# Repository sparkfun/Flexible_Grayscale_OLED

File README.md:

SparkFun Flexible Grayscale OLED Display Breakout Board
========================================

[*SparkFun Flexible Grayscale Display - 1.81" (LCD-14606)*](https://www.sparkfun.com/products/14606)

This is a small flexible, grayscale OLED display. That’s right, we said flexible. We’ve been hearing about flexible displays for years, it’s finally here! You can’t fold it like paper but this OLED from Wisechip can be bent to a 40mm radius without damage. The display is than 0.5mm thick, less than 0.5 grams, and can display some impressive graphics with great contrast.

The carrier board generates the 12V required to drive the OLED display. The carrier board also has a signal buffer so that you can drive the display from any 3.3V or 5V microcontroller. However, because of the nature of the TXB0104 you must power the board with 3.5V or more. Your microcontroller can be 3.3V or 5V but we recommend you power the carrier board with 5V.

Repository Contents
-------------------

* **/Datasheets** - Datasheets explaining screen characteristics
* **/Hardware** - Eagle design files (.brd, .sch)
* **/Production** - Test bed files and production panel files.

Documentation
--------------
* **[Arduino Library](https://github.com/sparkfun/SparkFun_SSD1320_OLED_Arduino_Library)** - Arduino library for drawing, graphics, text, etc.
* **[BMP to Array](https://github.com/sparkfun/BMPtoArray)** - Python script to convert bitmaps to an Arduino prog_mem array when outputting grayscale images to OLEDs.
* **[Hookup Guide](https://learn.sparkfun.com/tutorials/flexible-grayscale-oled-hookup-guide)** - Basic hookup guide for the SparkFun Flexible Grayscale OLED Display.

License Information
-------------------

This product is _**open source**_! 

Please review the LICENSE.md file for license information. 

If you have any questions or concerns on licensing, please contact techsupport@sparkfun.com.

Please use, reuse, and modify these files as you see fit. Please maintain attribution to SparkFun Electronics and release anyThing Development Board derivative under the same license.

Distributed as-is; no warranty is given.

- Your friends at SparkFun.

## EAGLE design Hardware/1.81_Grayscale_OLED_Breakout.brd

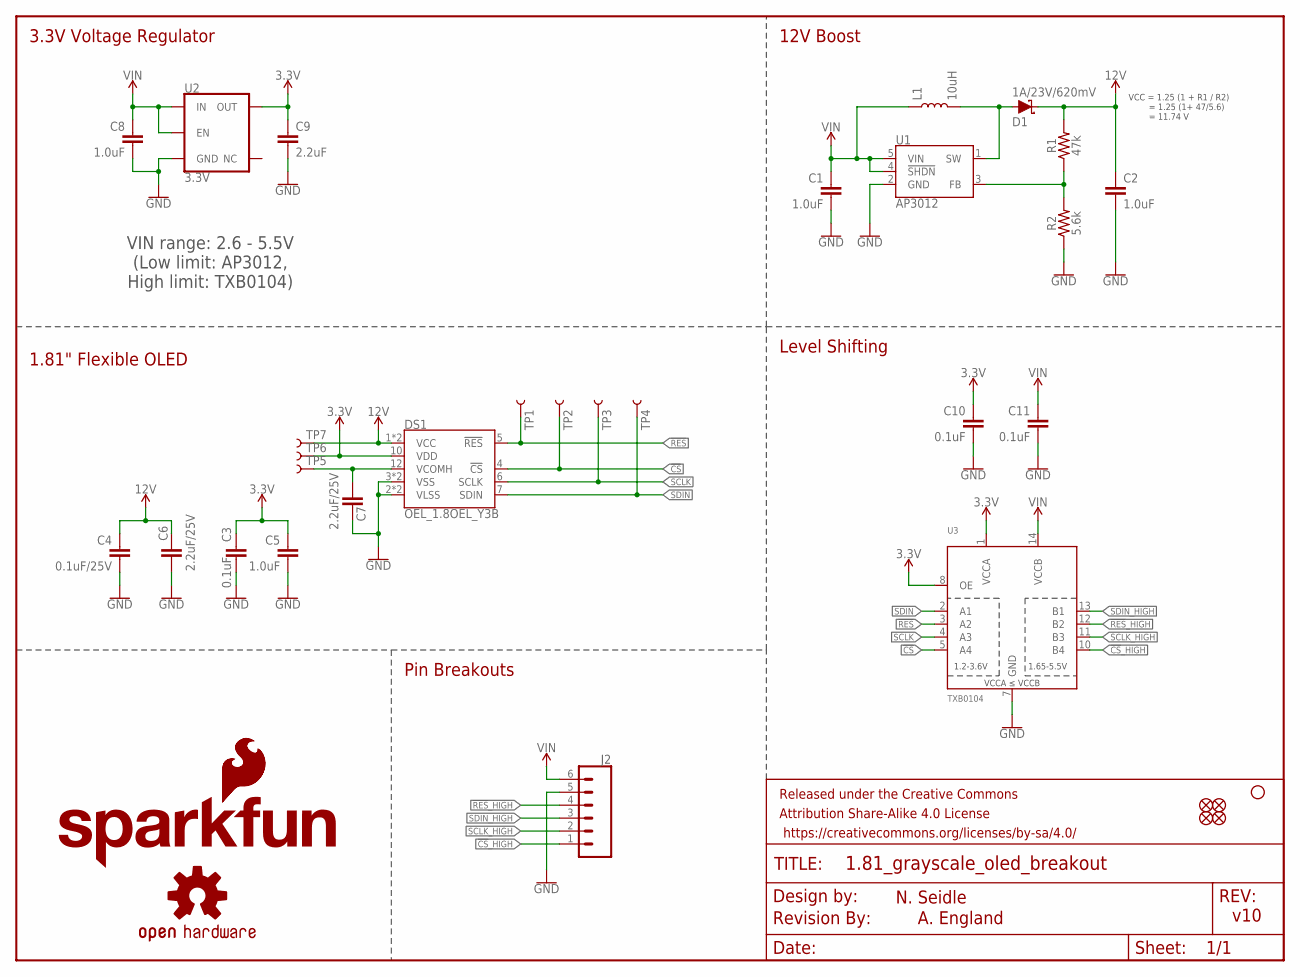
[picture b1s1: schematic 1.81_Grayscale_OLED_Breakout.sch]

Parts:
C1, C5, C8: 1.0uF; 0603
C2: 1.0uF; 0805
C3, C10, C11: 0.1uF; 0603
C4: 0.1uF/25V; 0603
C6, C7: 2.2uF/25V; 0805
C9: 2.2uF; 0603
D1: 1A/23V/620mV; SOD-323
DS1: OEL_1.8OEL_Y3B; OEL_1.8_FPC_Y3B
FD1, FD2, FD3, FD4: FIDUCIAL1X2; FIDUCIAL-1X2
FRAME1: FRAME-LETTER; CREATIVE_COMMONS
H2: STAND-OFF
J2: CONN_06NO_SILK_NO_POP; 1X06_NO_SILK
L1: 10uH; INDUCTOR_4.7UH
LOGO1: SFE_LOGO_NAME_FLAME.1_INCH; SFE_LOGO_NAME_FLAME_.1
LOGO2: REVISION
LOGO3: SFE_LOGO_FLAME.1_INCH; SFE_LOGO_FLAME_.1
LOGO4: OSHW-LOGOS; OSHW-LOGO-S
R1: 47k; 0603
R2: 5.6k; 0603
TP1, TP2, TP3, TP4, TP5, TP6, TP7: TEST-POINT3; PAD.03X.03
U1: AP3012; SOT23-5
U2: 3.3V; SOT23-5
U3: TXB0104; SO14

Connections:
3.3V: C3.1, C5.1, C9.1, C10.1, DS1.10 (VDD), TP6.P$1, U2.5 (OUT), U3.1 (VCCA), U3.8 (OE)
12V: C2.1, C4.1, C6.1, D1.C, DS1.1 (VCC), DS1.13 (VCC), R1.2, TP7.P$1
!CS!: DS1.4 (!CS!), TP2.P$1, U3.5 (A4)
!CS!_HIGH: J2.1, U3.10 (B4)
!RES!: DS1.5 (!RES!), TP1.P$1, U3.3 (A2)
!RES!_HIGH: J2.4, U3.12 (B2)
GND: C1.2, C2.2, C3.2, C4.2, C5.2, C6.2, C7.1, C8.2, C9.2, C10.2, C11.2, DS1.2 (VLSS), DS1.3 (VSS), DS1.8 (VSS), DS1.9 (VLSS), J2.5, R2.1, U1.2 (GND), U2.2 (GND), U3.7 (GND)
unnamed: C7.2, DS1.12 (VCOMH), TP5.P$1
unnamed: D1.A, L1.P$2 (2), U1.1 (SW)
unnamed: R1.1, R2.2, U1.3 (FB)
SCLK: DS1.6 (SCLK), TP3.P$1, U3.4 (A3)
SCLK_HIGH: J2.2, U3.11 (B3)
SDIN: DS1.7 (SDIN), TP4.P$1, U3.2 (A1)
SDIN_HIGH: J2.3, U3.13 (B1)
VIN: C1.1, C8.1, C11.1, J2.6, L1.P$1 (1), U1.4 (!SHDN!), U1.5 (VIN), U2.1 (IN), U2.3 (EN), U3.14 (VCCB)

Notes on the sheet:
VCC = 1.25 (1 + R1 / R2) = 1.25 (1+ 47/5.6) = 11.74 V
VIN range: 2.6 - 5.5V (Low limit: AP3012, High limit: TXB0104)
3.3V Voltage Regulator
12V Boost
1.81" Flexible OLED
Level Shifting
Pin Breakouts
v10
N. Seidle
A. England

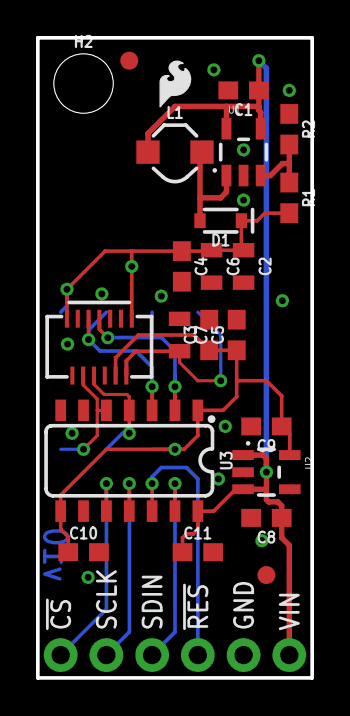
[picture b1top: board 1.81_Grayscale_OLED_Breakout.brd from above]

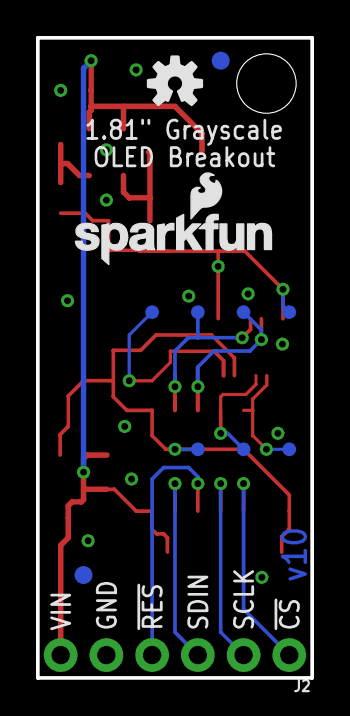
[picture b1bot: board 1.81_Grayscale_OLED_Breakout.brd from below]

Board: 2 copper layers, 15.2 x 35.6 mm, 37 parts (13 on the bottom side), 15 nets.

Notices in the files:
parts and their libraries:
SparkFun-Aesthetics: Licensing: Creative Commons ShareAlike 4.0 International - https://creativecommons.org/licenses/by-sa/4.0
SparkFun-Aesthetics: Released under the Creative Commons Attribution Share-Alike 4.0 License
SparkFun-Aesthetics: https://creativecommons.org/licenses/by-sa/4.0
